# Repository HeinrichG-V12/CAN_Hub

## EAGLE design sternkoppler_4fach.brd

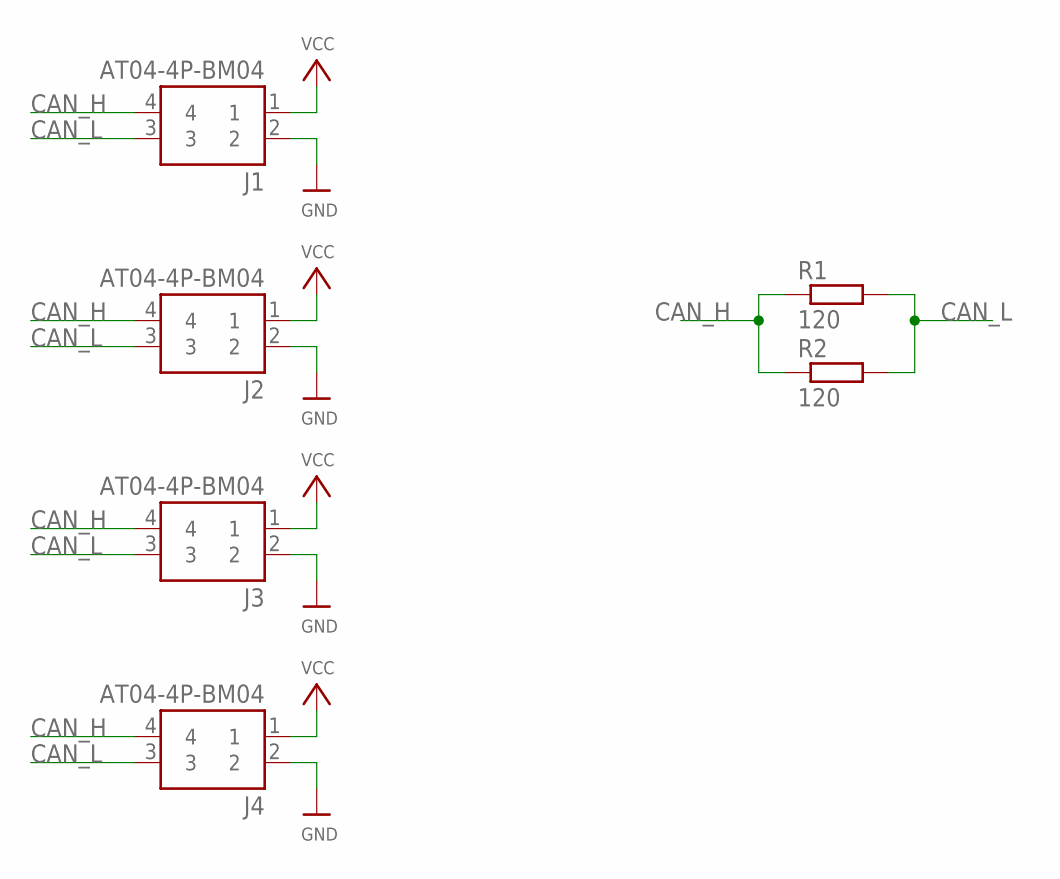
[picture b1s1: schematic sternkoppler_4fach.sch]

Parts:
J1, J2, J3, J4: AT04-4P-BM04; AT044PBM04
R1, R2: 120; R0805

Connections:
CAN_H: J1.4, J2.4, J3.4, J4.4, R1.1, R2.1
CAN_L: J1.3, J2.3, J3.3, J4.3, R1.2, R2.2
GND: J1.2, J2.2, J3.2, J4.2
VCC: J1.1, J2.1, J3.1, J4.1

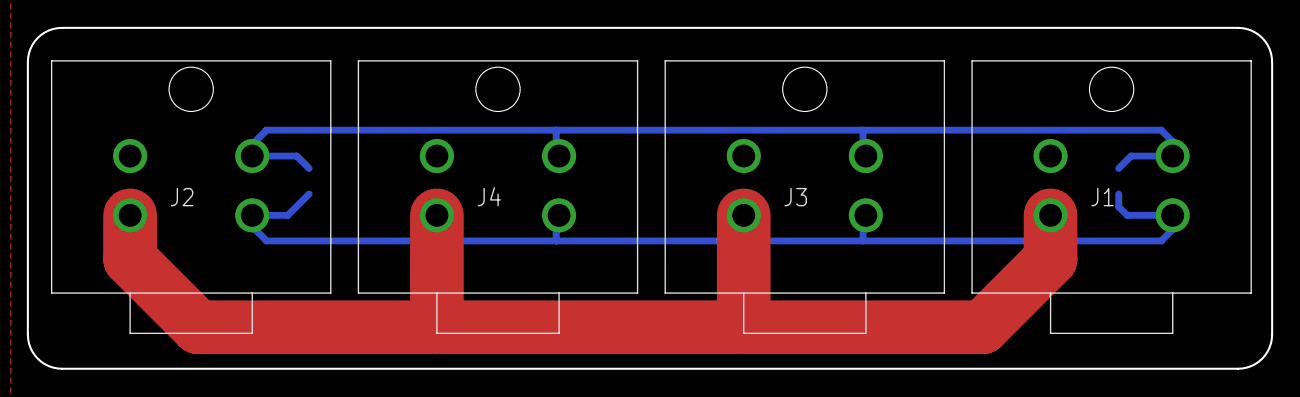
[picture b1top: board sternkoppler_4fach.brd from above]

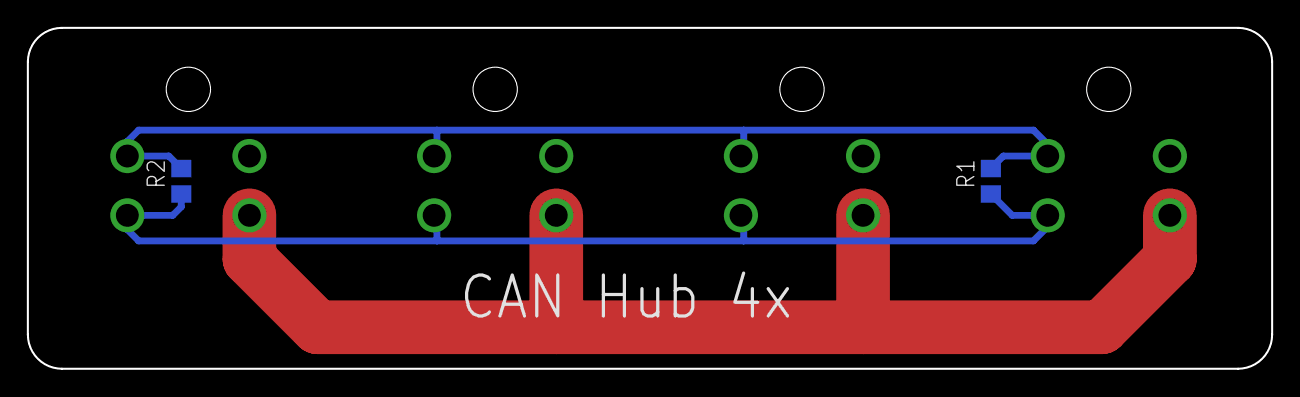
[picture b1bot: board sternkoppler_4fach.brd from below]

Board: 2 copper layers, 92.7 x 25.4 mm, 6 parts (2 on the bottom side), 4 nets.

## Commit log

2022-09-05 initial import
2022-09-29 pictures added

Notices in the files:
parts and their libraries:
microbuilder: This work is placed in the public domain, and may be freely used for commercial and non-commercial work with the following conditions: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
